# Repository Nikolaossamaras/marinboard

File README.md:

# MariBoard
>A costum keyboard featuring the anime Character Marin Kitagawa

## What is it
It's a costum keyboard with the thematic of Marin kitagawa from the anime My-dress-up-darling by cloverworks. It's layout is keycool kc84 75% . It includes 84 keys & an oled diplay and it's powered by in raspberry pi pico W , allowing it to connect to the internet in order to display information to the oled display like the Time , date & Weather

## Why i built it?

I really love anime and my favourite character is Marin Kitagawa. I also like electronics and making projects so i sat down and though which will be my next project and i decided on this one a CUSTOM KEYBOARD that is designed with diffrent Marin Kitagawa and dress-up-darling pictures.

## PCB Preview

---

## Schematic

---

## CAD

## PCB assembly

## Requirements

| Product | quantity |
| --- | --- |
| OLED Module 128x32 0.91" i2c | 1pc |
| Raspberry Pi Pico W | 1pc |
| 1N4148W diodes | 84pcs |
| costum pcb | 1pc |
| cherry mx switches | 84pcs |
| keycaps | 84 pcs |
| knurled nuts brass m3 | 4pcs |
| 3D printed case | 1pc |

## Tools 

| Tool |
| --- |
| soldering station/iron |
| 3d printer |

## How to assemble it?

### 1st step
your first step is cloning this repo to your Pc so you have all the required files

### 2nd step

Get your pcb , go to a pcb production company and upload the gerber.zip file on their site and order the board

### 3rd step

While you wait for your pcb you can start 3d printing your case which is in Cad folder, there you will see 2 files both are the same one but diffrent format.

> if you don't have a 3d printer you can 3d print it from the same company from which you ordered your pcb

### 4th step 

Now that you have the pcb you will need to solder everything together
if you get an assembled board you wont need to solder the diodes as the are already will come installed , but if you didn't 
your next step is to solder the diodes together on the board like instructed in the schematic

### 5th step
when you finish with the diodes check them with a multimeter to check if they are connected the correct way

### 6th step
now solder the microcontroller and the push button

### 7th step 
solder the oled display in place

### 8th step 
add the switches to the top pcb in order and then put it on top of the middle pcb(main pcb), be careful to align every switch correctly in order the soldering of them to procced smoothly

### 9th step 
add nuts to the 3d printed case at the button 
then place on top of it the pcb's in order (first the bottom , then the main and then the top one) after that pass a screw in each corner mounting hole of the pcb until it's reached the nut , be careful not to damage the main board

### 10th step 
You will need to download the latest .uf2 stable file on Circuitpython for pico W (make sure it's the W not the normal version)

### 11th step
hold the bootsel button on the board while inserting the board to your pc release the button when it's connected **do this step before soldering the top and main pcb together**

### 12th step 

copy the .uf2 file to the microcontroller

the board will reboot and then a drove called ```Circuitpython``` should appear 

### 13th step
Your main program must be named code.py (or main.py) and placed at the root of CIRCUITPY
For libraries , grab the matching version of the CircuitPython Library Bundle and copy the needed .mpy files into a /lib folder on CIRCUITPY

### 14th step
when you upload the code to the drive it should become an input meaning the drive will disapear

## Licence

This project is under the MIT licence

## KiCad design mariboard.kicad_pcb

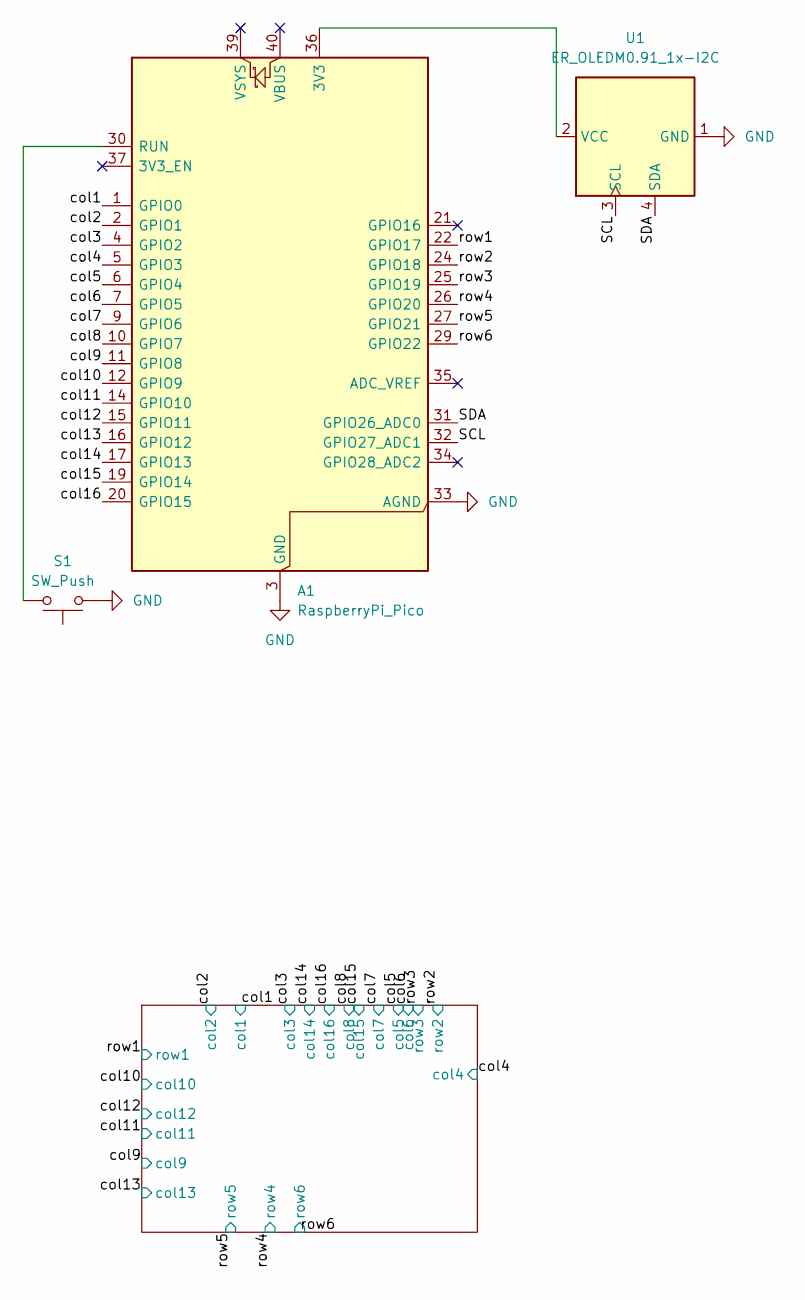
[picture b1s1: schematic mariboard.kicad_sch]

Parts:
A1: RaspberryPi_Pico; RaspberryPi_Pico_Common_Unspecified
S1: SW_Push; SW_PUSH_6mm
U1: ER_OLEDM0.91_1x-I2C

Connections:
/SCL: A1.32 (GPIO27_ADC1), U1.3 (SCL)
/SDA: A1.31 (GPIO26_ADC0), U1.4 (SDA)
/col1: A1.1 (GPIO0); also elsewhere on the board
/col2: A1.2 (GPIO1); also elsewhere on the board
/col3: A1.4 (GPIO2); also elsewhere on the board
/col4: A1.5 (GPIO3); also elsewhere on the board
/col5: A1.6 (GPIO4); also elsewhere on the board
/col6: A1.7 (GPIO5); also elsewhere on the board
/col7: A1.9 (GPIO6); also elsewhere on the board
/col8: A1.10 (GPIO7); also elsewhere on the board
/col9: A1.11 (GPIO8); also elsewhere on the board
/col10: A1.12 (GPIO9); also elsewhere on the board
/col11: A1.14 (GPIO10); also elsewhere on the board
/col12: A1.15 (GPIO11); also elsewhere on the board
/col13: A1.16 (GPIO12); also elsewhere on the board
/col14: A1.17 (GPIO13); also elsewhere on the board
/col15: A1.19 (GPIO14); also elsewhere on the board
/col16: A1.20 (GPIO15); also elsewhere on the board
/row1: A1.22 (GPIO17); also elsewhere on the board
/row2: A1.24 (GPIO18); also elsewhere on the board
/row3: A1.25 (GPIO19); also elsewhere on the board
/row4: A1.26 (GPIO20); also elsewhere on the board
/row5: A1.27 (GPIO21); also elsewhere on the board
/row6: A1.29 (GPIO22); also elsewhere on the board
GND: A1.3 (GND), A1.8 (GND), A1.13 (GND), A1.18 (GND), A1.23 (GND), A1.28 (GND), A1.33 (AGND), A1.38 (GND), S1.1, U1.1 (GND)
unnamed: A1.36 (3V3), U1.2 (VCC)
unnamed: A1.30 (RUN), S1.2

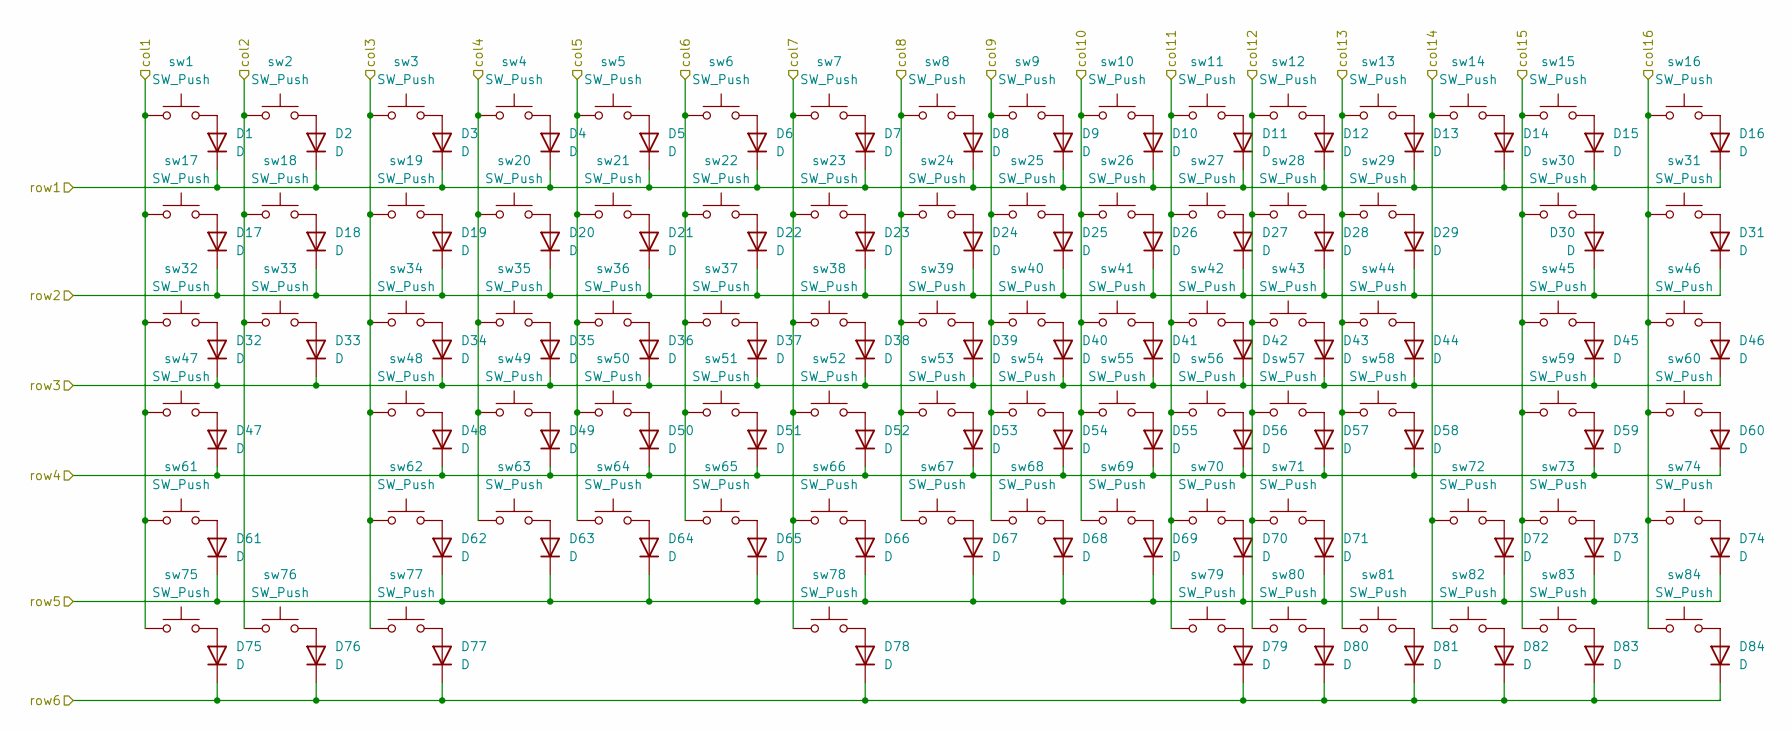
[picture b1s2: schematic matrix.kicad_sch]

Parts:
D1, D2, D3, D4, D5, D6, D7, D8, D9, D10, D11, D12, D13, D14, D15, D16, D17, D18, D19, D20, D21, D22, D23, D24, D25, D26, D27, D28, D29, D30, D31, D32, D33, D34, D35, D36, D37, D38, D39, D40, D41, D42, D43, D44, D45, D46, D47, D48, D49, D50, D51, D52, D53, D54, D55, D56, D57, D58, D59, D60, D61, D62, D63, D64, D65, D66, D67, D68, D69, D70, D71, D72, D73, D74, D75, D76, D77, D78, D79, D80, D81, D82, D83, D84: D; D_SOD-123
sw1, sw2, sw3, sw4, sw5, sw6, sw7, sw8, sw9, sw10, sw11, sw12, sw13, sw14, sw15, sw16, sw17, sw18, sw19, sw20, sw21, sw22, sw23, sw24, sw25, sw26, sw27, sw28, sw29, sw31, sw33, sw34, sw35, sw36, sw37, sw38, sw39, sw40, sw41, sw42, sw43, sw44, sw46, sw48, sw49, sw50, sw51, sw52, sw53, sw54, sw55, sw56, sw57, sw58, sw60, sw62, sw63, sw64, sw65, sw66, sw67, sw68, sw69, sw70, sw71, sw73, sw74, sw79, sw80, sw81, sw82, sw83, sw84: SW_Push; SW_Cherry_MX_1.00u_PCB
sw30: SW_Push; SW_Cherry_MX_2.00u_PCB
sw32, sw45: SW_Push; SW_Cherry_MX_1.50u_PCB
sw47, sw72: SW_Push; SW_Cherry_MX_1.75u_PCB
sw59, sw61: SW_Push; SW_Cherry_MX_2.25u_PCB
sw75, sw76, sw77: SW_Push; SW_Cherry_MX_1.25u_PCB
sw78: SW_Push; SW_Cherry_MX_6.25u_PCB

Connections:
/col1: sw1.1, sw17.1, sw32.1, sw47.1, sw61.1, sw75.1; also elsewhere on the board
/col2: sw2.1, sw18.1, sw33.1, sw76.1; also elsewhere on the board
/col3: sw3.1, sw19.1, sw34.1, sw48.1, sw62.1, sw77.1; also elsewhere on the board
/col4: sw4.1, sw20.1, sw35.1, sw49.1, sw63.1; also elsewhere on the board
/col5: sw5.1, sw21.1, sw36.1, sw50.1, sw64.1; also elsewhere on the board
/col6: sw6.1, sw22.1, sw37.1, sw51.1, sw65.1; also elsewhere on the board
/col7: sw7.1, sw23.1, sw38.1, sw52.1, sw66.1, sw78.1; also elsewhere on the board
/col8: sw8.1, sw24.1, sw39.1, sw53.1, sw67.1; also elsewhere on the board
/col9: sw9.1, sw25.1, sw40.1, sw54.1, sw68.1; also elsewhere on the board
/col10: sw10.1, sw26.1, sw41.1, sw55.1, sw69.1; also elsewhere on the board
/col11: sw11.1, sw27.1, sw42.1, sw56.1, sw70.1, sw79.1; also elsewhere on the board
/col12: sw12.1, sw28.1, sw43.1, sw57.1, sw71.1, sw80.1; also elsewhere on the board
/col13: sw13.1, sw29.1, sw44.1, sw58.1, sw81.1; also elsewhere on the board
/col14: sw14.1, sw72.1, sw82.1; also elsewhere on the board
/col15: sw15.1, sw30.1, sw45.1, sw59.1, sw73.1, sw83.1; also elsewhere on the board
/col16: sw16.1, sw31.1, sw46.1, sw60.1, sw74.1, sw84.1; also elsewhere on the board
/row1: D1.1 (K), D2.1 (K), D3.1 (K), D4.1 (K), D5.1 (K), D6.1 (K), D7.1 (K), D8.1 (K), D9.1 (K), D10.1 (K), D11.1 (K), D12.1 (K), D13.1 (K), D14.1 (K), D15.1 (K), D16.1 (K); also elsewhere on the board
/row2: D17.1 (K), D18.1 (K), D19.1 (K), D20.1 (K), D21.1 (K), D22.1 (K), D23.1 (K), D24.1 (K), D25.1 (K), D26.1 (K), D27.1 (K), D28.1 (K), D29.1 (K), D30.1 (K), D31.1 (K); also elsewhere on the board
/row3: D32.1 (K), D33.1 (K), D34.1 (K), D35.1 (K), D36.1 (K), D37.1 (K), D38.1 (K), D39.1 (K), D40.1 (K), D41.1 (K), D42.1 (K), D43.1 (K), D44.1 (K), D45.1 (K), D46.1 (K); also elsewhere on the board
/row4: D47.1 (K), D48.1 (K), D49.1 (K), D50.1 (K), D51.1 (K), D52.1 (K), D53.1 (K), D54.1 (K), D55.1 (K), D56.1 (K), D57.1 (K), D58.1 (K), D59.1 (K), D60.1 (K); also elsewhere on the board
/row5: D61.1 (K), D62.1 (K), D63.1 (K), D64.1 (K), D65.1 (K), D66.1 (K), D67.1 (K), D68.1 (K), D69.1 (K), D70.1 (K), D71.1 (K), D72.1 (K), D73.1 (K), D74.1 (K); also elsewhere on the board
/row6: D75.1 (K), D76.1 (K), D77.1 (K), D78.1 (K), D79.1 (K), D80.1 (K), D81.1 (K), D82.1 (K), D83.1 (K), D84.1 (K); also elsewhere on the board
unnamed: D1.2 (A), sw1.2
unnamed: D2.2 (A), sw2.2
unnamed: D3.2 (A), sw3.2
unnamed: D4.2 (A), sw4.2
unnamed: D5.2 (A), sw5.2
unnamed: D6.2 (A), sw6.2
unnamed: D7.2 (A), sw7.2
unnamed: D8.2 (A), sw8.2
unnamed: D9.2 (A), sw9.2
unnamed: D10.2 (A), sw10.2
unnamed: D11.2 (A), sw11.2
unnamed: D12.2 (A), sw12.2
unnamed: D13.2 (A), sw13.2
unnamed: D14.2 (A), sw14.2
unnamed: D15.2 (A), sw15.2
unnamed: D16.2 (A), sw16.2
unnamed: D17.2 (A), sw17.2
unnamed: D18.2 (A), sw18.2
unnamed: D19.2 (A), sw19.2
unnamed: D20.2 (A), sw20.2
unnamed: D21.2 (A), sw21.2
unnamed: D22.2 (A), sw22.2
unnamed: D23.2 (A), sw23.2
unnamed: D24.2 (A), sw24.2
unnamed: D25.2 (A), sw25.2
unnamed: D26.2 (A), sw26.2
unnamed: D27.2 (A), sw27.2
unnamed: D28.2 (A), sw28.2
unnamed: D29.2 (A), sw29.2
unnamed: D30.2 (A), sw30.2
unnamed: D31.2 (A), sw31.2
unnamed: D32.2 (A), sw32.2
unnamed: D33.2 (A), sw33.2
unnamed: D34.2 (A), sw34.2
unnamed: D35.2 (A), sw35.2
unnamed: D36.2 (A), sw36.2
unnamed: D37.2 (A), sw37.2
unnamed: D38.2 (A), sw38.2
unnamed: D39.2 (A), sw39.2
unnamed: D40.2 (A), sw40.2
unnamed: D41.2 (A), sw41.2
unnamed: D42.2 (A), sw42.2
unnamed: D43.2 (A), sw43.2
unnamed: D44.2 (A), sw44.2
unnamed: D45.2 (A), sw45.2
unnamed: D46.2 (A), sw46.2
unnamed: D47.2 (A), sw47.2
unnamed: D48.2 (A), sw48.2
unnamed: D49.2 (A), sw49.2
unnamed: D50.2 (A), sw50.2
unnamed: D51.2 (A), sw51.2
unnamed: D52.2 (A), sw52.2
unnamed: D53.2 (A), sw53.2
unnamed: D54.2 (A), sw54.2
unnamed: D55.2 (A), sw55.2
unnamed: D56.2 (A), sw56.2
unnamed: D57.2 (A), sw57.2
unnamed: D58.2 (A), sw58.2
unnamed: D59.2 (A), sw59.2
unnamed: D60.2 (A), sw60.2
unnamed: D61.2 (A), sw61.2
unnamed: D62.2 (A), sw62.2
unnamed: D63.2 (A), sw63.2
unnamed: D64.2 (A), sw64.2
unnamed: D65.2 (A), sw65.2
unnamed: D66.2 (A), sw66.2
unnamed: D67.2 (A), sw67.2
unnamed: D68.2 (A), sw68.2
unnamed: D69.2 (A), sw69.2
unnamed: D70.2 (A), sw70.2
unnamed: D71.2 (A), sw71.2
unnamed: D72.2 (A), sw72.2
unnamed: D73.2 (A), sw73.2
unnamed: D74.2 (A), sw74.2
unnamed: D75.2 (A), sw75.2
unnamed: D76.2 (A), sw76.2
unnamed: D77.2 (A), sw77.2
unnamed: D78.2 (A), sw78.2
unnamed: D79.2 (A), sw79.2
unnamed: D80.2 (A), sw80.2
unnamed: D81.2 (A), sw81.2
unnamed: D82.2 (A), sw82.2
unnamed: D83.2 (A), sw83.2
unnamed: D84.2 (A), sw84.2

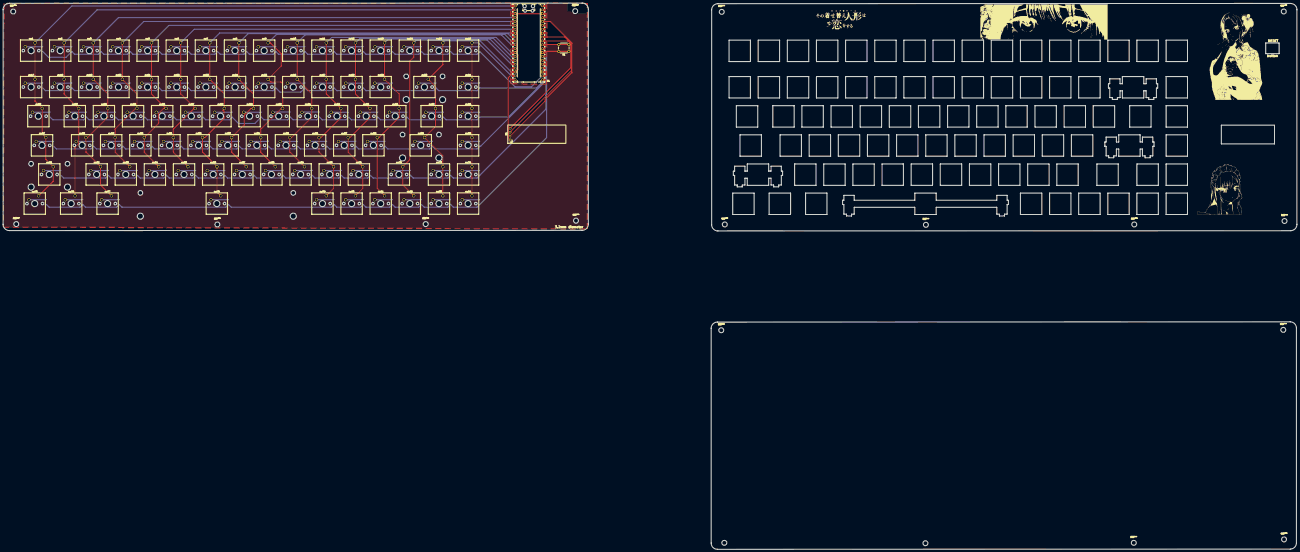
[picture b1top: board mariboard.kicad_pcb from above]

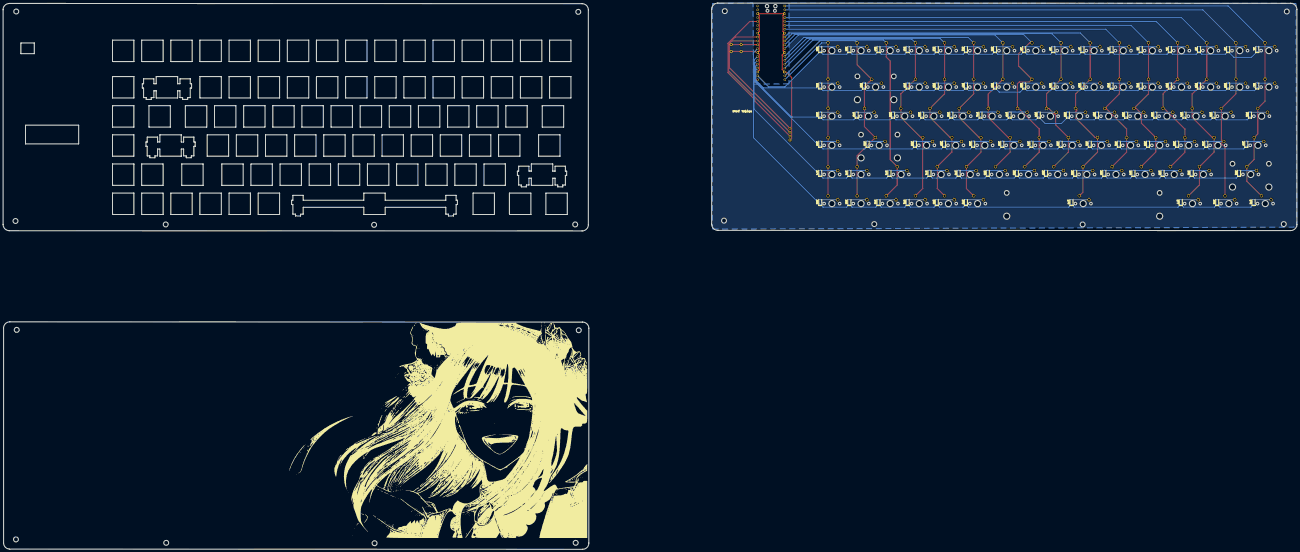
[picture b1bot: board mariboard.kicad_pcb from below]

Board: 2 copper layers, 382.7 x 148.8 mm, 171 parts (84 on the bottom side), 111 nets.
